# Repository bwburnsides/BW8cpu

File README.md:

# 👾 BW8cpu

The BW8cpu is a homemade CPU built with discrete TTL logic chips on custom designed PCBs. It has a target clock rate of approximately 6 MHz, and is comparable to the Motorola 6809, and more specifically the Hitachi 6309. A larger computer system is built around the CPU in the form a full peripheral suite that allows the BW8cpu to perform as an integrated computer similar to the Commodore 64 and NES. From a hardware perspective, the BW8cpu exceeds these systems in capability and usability in most regards. Its my hope that the system will eventually exceed its predecessors from a software perspective as well.

The project is originally inspired by Ben Eater's [8-bit breadboard CPU](https://eater.net/8bit) and his [breadboard MOS 6502 computer](https://eater.net/6502). However, ultimately the micro-architecture takes more cues from James Sharman's [8-bit pipelined CPU](https://www.youtube.com/watch?v=3iHag4k4yEg&list=PLFhc0MFC8MiCDOh3cGFji3qQfXziB9yOw). This project would not be possible without the support of many individuals present on James Sharman's Discord server, notably [rj45](https://github.com/rj45/rj32), Quandary, Artentus, and [Louis Jewett](https://www.youtube.com/channel/UCsxBT-Jh5pMDU-uEN_EUXtg/featured).

This project is extremely ambitious and long running. This repository will maintain documentation and descriptions of the existent and planned features, as well as supporting schematics and source code files.

--- 

## Features

- 8-bit CPU with 16-bit addressing
- Up to 768 opcodes across 50+ instructions (CISC ISA)
- Dual 8-bit accumulators (A, B) accessible also as one 16-bit accumulator (E)
- Two additional 8-bit General Purpose Registers (C, D)
- Full 16-bit Stack Pointer (SP) and Program Counters (PC)
- Configurable Direct Page addressing (movable Zero Page)
- Two 16-bit Index Registers (X, Y)
- 32-function ALU with 4 flags (Carry, Zero, Overflow, Sign)
- Single IRQ source
- Partially configurable hardware memory map
- Writable Control Store

---
## Architecture Overview

- [von Neumann architecture](https://en.wikipedia.org/wiki/Von_Neumann_architecture) with shared program and data address space
- Vertical microcode (heavily encoded) with 32-bit Control Bus
- Direct to address bus assertions without MAR
- No instruction pipelining - up to 8 clocks / instruction

---

## Expansion & Peripherals

- IO is memory mapped
- Reference Memory Map features:
    - 8 KB shadow RAM kernel space
    - 256 bytes IO space
    - 21.75 KB fixed RAM space
    - 2 KB stack space
    - 32 KB total bankable space
- Plans for full peripheral suite:
    - Programmable Interrupt Controller with 8 interrupt sources
    - VGA Video Card with output at 320x240
    - PS/2 keyboard input
    - Programmable Sound Generator with 4 voices
    - SPI Controller for SD card-based persistent storage
    - RS-232 UART networking interface

---

## Tool Chain

- Simulation with [Digital](https://github.com/hneemann/Digital)
- Emulation with [Rust](https://www.rust-lang.org/)
- Schematics and PCB layout with [KiCAD](https://www.kicad.org/)
- Assembler with [customasm](https://github.com/hlorenzi/customasm)
- Microcode development with customasm
- High level programming with [MHL](https://github.com/Artentus/MHL)

---

## Explore

🔧 [ISA](docs/instruction-set-architecture.md)

🧮 [ALU](docs/arithmetic-logic-unit.md)

🚥 [CU](docs/control-unit.md)

📺 [VGA](docs/video-card.md)

💾 [SPI](docs/spi.md)

📢 [PSG](docs/sound-card.md)

📡 [UART](docs/uart.md)

🎛 [Emulator](docs/emulator.md)

🎯 [Simulator](docs/simulator.md)

🗺 [Memory Map](docs/memory-map.md)

🏗 [Assembler](docs/assembler.md)

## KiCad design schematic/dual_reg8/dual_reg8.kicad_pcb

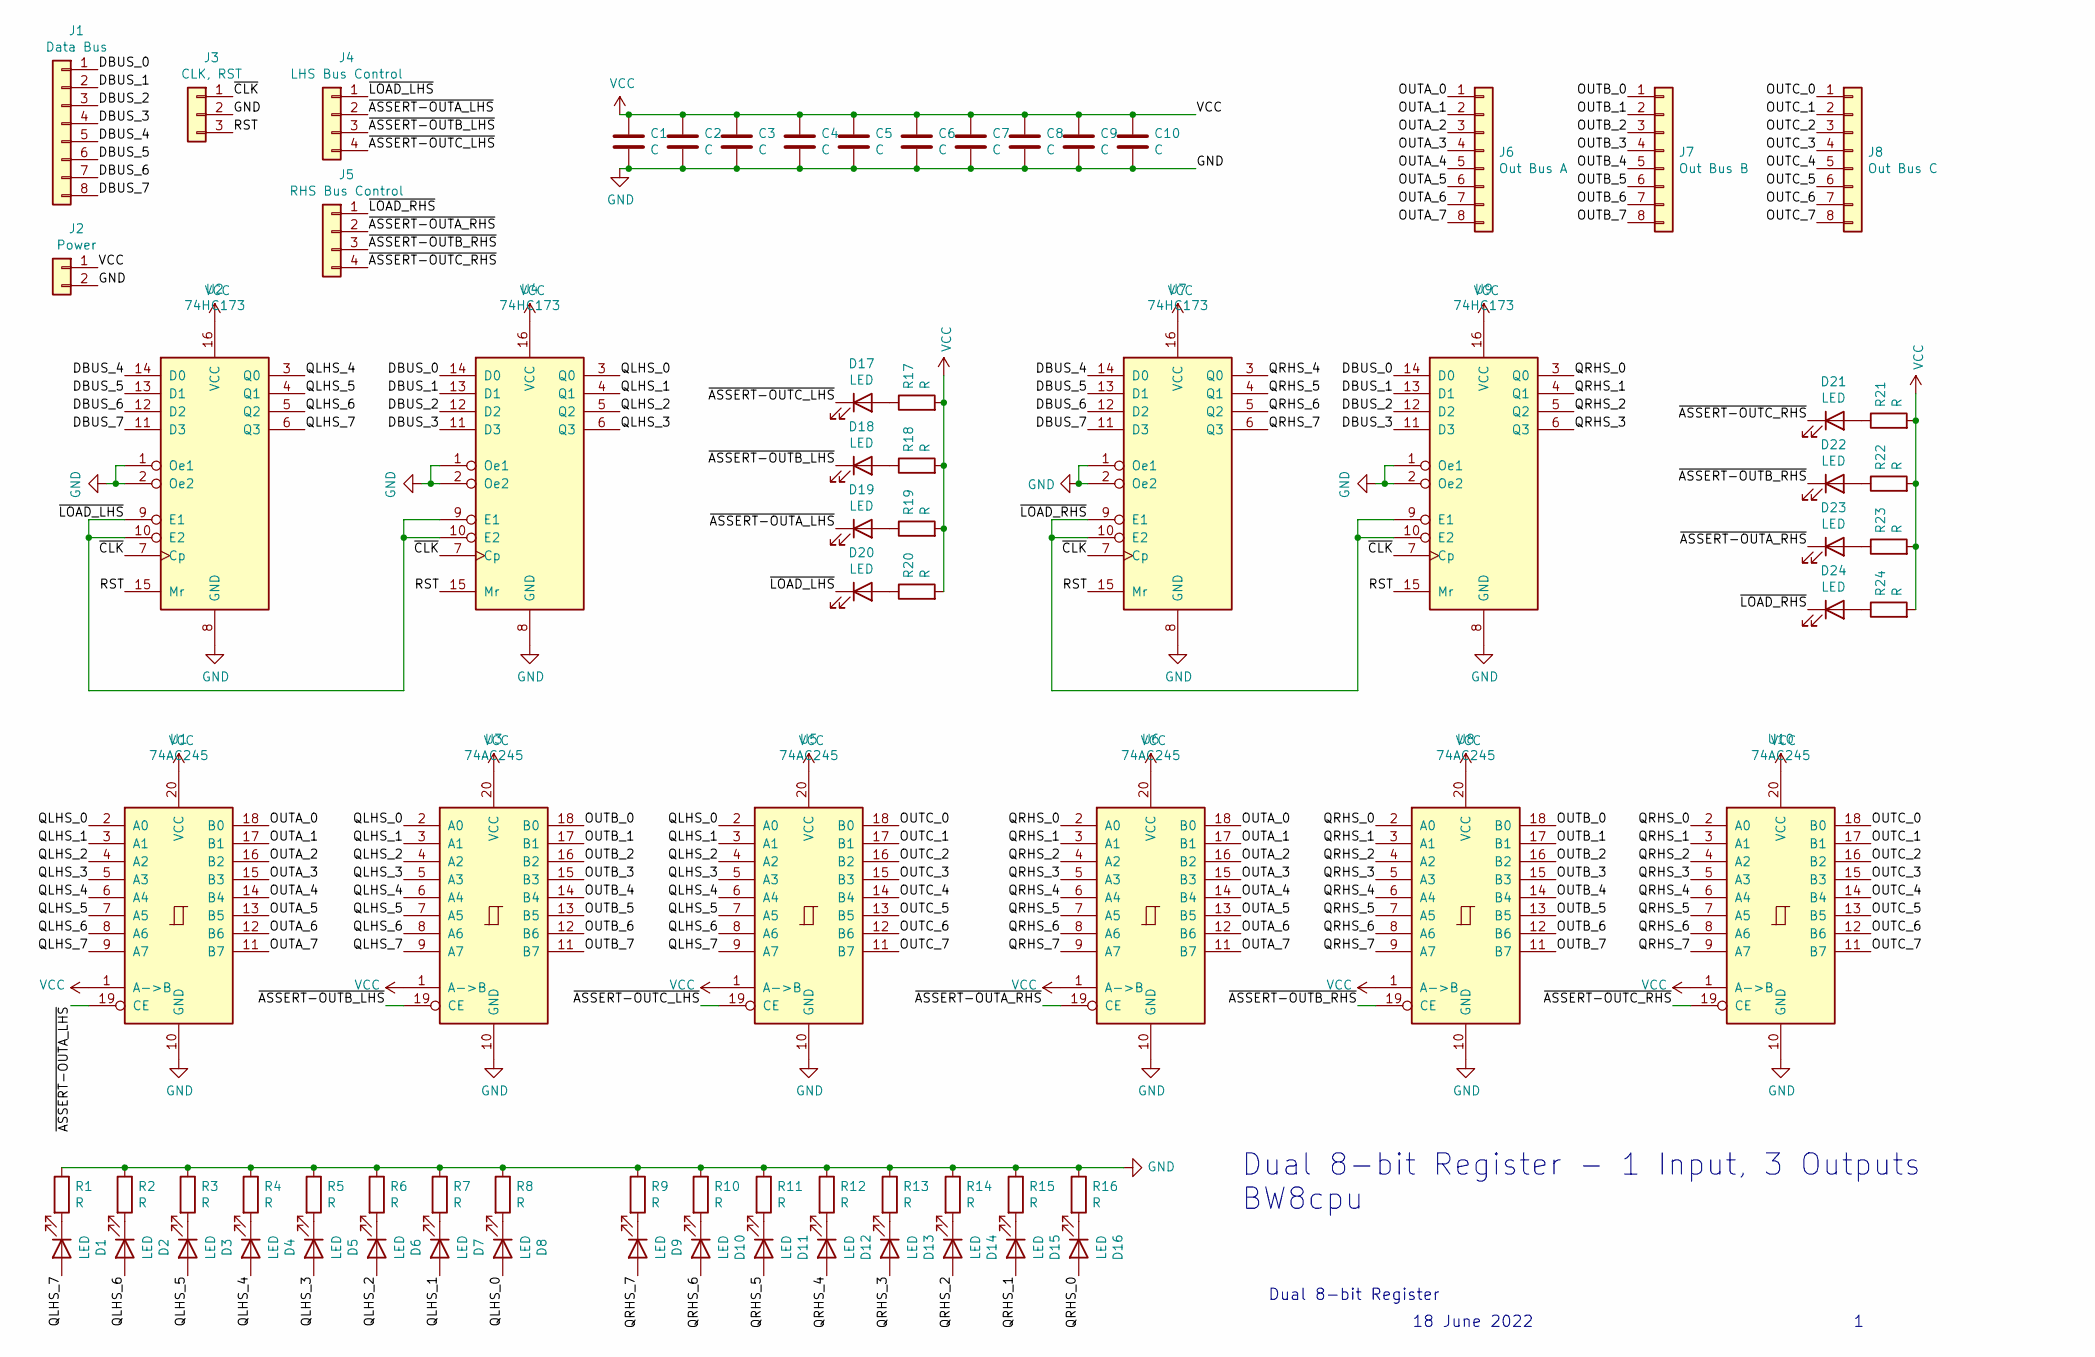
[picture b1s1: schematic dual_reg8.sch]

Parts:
C1, C2, C3, C4, C5, C6, C7, C8, C9, C10: C; C_Disc_D3.0mm_W1.6mm_P2.50mm
D1, D2, D3, D4, D5, D6, D7, D8, D9, D10, D11, D12, D13, D14, D15, D16, D17, D18, D19, D20, D21, D22, D23, D24: LED; LED_D2.0mm_W4.8mm_H2.5mm_FlatTop
J1: Data Bus; PinSocket_1x08_P2.54mm_Vertical
J2: Power; PinSocket_1x02_P2.54mm_Vertical
J3: CLK, RST; PinSocket_1x03_P2.54mm_Vertical
J4: LHS Bus Control; PinSocket_1x04_P2.54mm_Vertical
J5: RHS Bus Control; PinSocket_1x04_P2.54mm_Vertical
J6: Out Bus A; PinSocket_1x08_P2.54mm_Vertical
J7: Out Bus B; PinSocket_1x08_P2.54mm_Vertical
J8: Out Bus C; PinSocket_1x08_P2.54mm_Vertical
R1, R2, R3, R4, R5, R6, R7, R8, R9, R10, R11, R12, R13, R14, R15, R16, R17, R18, R19, R20, R21, R22, R23, R24: R; R_Axial_DIN0204_L3.6mm_D1.6mm_P5.08mm_Horizontal
U1, U3, U5, U6, U8, U10: 74AC245; DIP-20_W7.62mm
U2, U4, U7, U9: 74HC173; DIP-16_W7.62mm

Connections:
/DBUS_0: J1.1, U4.14 (D0), U9.14 (D0)
/DBUS_1: J1.2, U4.13 (D1), U9.13 (D1)
/DBUS_2: J1.3, U4.12 (D2), U9.12 (D2)
/DBUS_3: J1.4, U4.11 (D3), U9.11 (D3)
/DBUS_4: J1.5, U2.14 (D0), U7.14 (D0)
/DBUS_5: J1.6, U2.13 (D1), U7.13 (D1)
/DBUS_6: J1.7, U2.12 (D2), U7.12 (D2)
/DBUS_7: J1.8, U2.11 (D3), U7.11 (D3)
/OUTA_0: J6.1, U1.18 (B0), U6.18 (B0)
/OUTA_1: J6.2, U1.17 (B1), U6.17 (B1)
/OUTA_2: J6.3, U1.16 (B2), U6.16 (B2)
/OUTA_3: J6.4, U1.15 (B3), U6.15 (B3)
/OUTA_4: J6.5, U1.14 (B4), U6.14 (B4)
/OUTA_5: J6.6, U1.13 (B5), U6.13 (B5)
/OUTA_6: J6.7, U1.12 (B6), U6.12 (B6)
/OUTA_7: J6.8, U1.11 (B7), U6.11 (B7)
/OUTB_0: J7.1, U3.18 (B0), U8.18 (B0)
/OUTB_1: J7.2, U3.17 (B1), U8.17 (B1)
/OUTB_2: J7.3, U3.16 (B2), U8.16 (B2)
/OUTB_3: J7.4, U3.15 (B3), U8.15 (B3)
/OUTB_4: J7.5, U3.14 (B4), U8.14 (B4)
/OUTB_5: J7.6, U3.13 (B5), U8.13 (B5)
/OUTB_6: J7.7, U3.12 (B6), U8.12 (B6)
/OUTB_7: J7.8, U3.11 (B7), U8.11 (B7)
/OUTC_0: J8.1, U5.18 (B0), U10.18 (B0)
/OUTC_1: J8.2, U5.17 (B1), U10.17 (B1)
/OUTC_2: J8.3, U5.16 (B2), U10.16 (B2)
/OUTC_3: J8.4, U5.15 (B3), U10.15 (B3)
/OUTC_4: J8.5, U5.14 (B4), U10.14 (B4)
/OUTC_5: J8.6, U5.13 (B5), U10.13 (B5)
/OUTC_6: J8.7, U5.12 (B6), U10.12 (B6)
/OUTC_7: J8.8, U5.11 (B7), U10.11 (B7)
/QLHS_0: D8.2 (A), U1.2 (A0), U3.2 (A0), U4.3 (Q0), U5.2 (A0)
/QLHS_1: D7.2 (A), U1.3 (A1), U3.3 (A1), U4.4 (Q1), U5.3 (A1)
/QLHS_2: D6.2 (A), U1.4 (A2), U3.4 (A2), U4.5 (Q2), U5.4 (A2)
/QLHS_3: D5.2 (A), U1.5 (A3), U3.5 (A3), U4.6 (Q3), U5.5 (A3)
/QLHS_4: D4.2 (A), U1.6 (A4), U2.3 (Q0), U3.6 (A4), U5.6 (A4)
/QLHS_5: D3.2 (A), U1.7 (A5), U2.4 (Q1), U3.7 (A5), U5.7 (A5)
/QLHS_6: D2.2 (A), U1.8 (A6), U2.5 (Q2), U3.8 (A6), U5.8 (A6)
/QLHS_7: D1.2 (A), U1.9 (A7), U2.6 (Q3), U3.9 (A7), U5.9 (A7)
/QRHS_0: D16.2 (A), U6.2 (A0), U8.2 (A0), U9.3 (Q0), U10.2 (A0)
/QRHS_1: D15.2 (A), U6.3 (A1), U8.3 (A1), U9.4 (Q1), U10.3 (A1)
/QRHS_2: D14.2 (A), U6.4 (A2), U8.4 (A2), U9.5 (Q2), U10.4 (A2)
/QRHS_3: D13.2 (A), U6.5 (A3), U8.5 (A3), U9.6 (Q3), U10.5 (A3)
/QRHS_4: D12.2 (A), U6.6 (A4), U7.3 (Q0), U8.6 (A4), U10.6 (A4)
/QRHS_5: D11.2 (A), U6.7 (A5), U7.4 (Q1), U8.7 (A5), U10.7 (A5)
/QRHS_6: D10.2 (A), U6.8 (A6), U7.5 (Q2), U8.8 (A6), U10.8 (A6)
/QRHS_7: D9.2 (A), U6.9 (A7), U7.6 (Q3), U8.9 (A7), U10.9 (A7)
/RST: J3.3, U2.15 (Mr), U4.15 (Mr), U7.15 (Mr), U9.15 (Mr)
/~ASSERT-OUTA_LHS: D19.1 (K), J4.2, U1.19 (CE)
/~ASSERT-OUTA_RHS: D23.1 (K), J5.2, U6.19 (CE)
/~ASSERT-OUTB_LHS: D18.1 (K), J4.3, U3.19 (CE)
/~ASSERT-OUTB_RHS: D22.1 (K), J5.3, U8.19 (CE)
/~ASSERT-OUTC_LHS: D17.1 (K), J4.4, U5.19 (CE)
/~ASSERT-OUTC_RHS: D21.1 (K), J5.4, U10.19 (CE)
/~CLK: J3.1, U2.7 (Cp), U4.7 (Cp), U7.7 (Cp), U9.7 (Cp)
/~LOAD_LHS: D20.1 (K), J4.1, U2.9 (E1), U2.10 (E2), U4.9 (E1), U4.10 (E2)
/~LOAD_RHS: D24.1 (K), J5.1, U7.9 (E1), U7.10 (E2), U9.9 (E1), U9.10 (E2)
GND: C1.2, C2.2, C3.2, C4.2, C5.2, C6.2, C7.2, C8.2, C9.2, C10.2, J2.2, J3.2, R1.1, R2.1, R3.1, R4.1, R5.1, R6.1, R7.1, R8.1, R9.1, R10.1, R11.1, R12.1, R13.1, R14.1, R15.1, R16.1, U1.10 (GND), U2.1 (Oe1), U2.2 (Oe2), U2.8 (GND), U3.10 (GND), U4.1 (Oe1), U4.2 (Oe2), U4.8 (GND), U5.10 (GND), U6.10 (GND), U7.1 (Oe1), U7.2 (Oe2), U7.8 (GND), U8.10 (GND), U9.1 (Oe1), U9.2 (Oe2), U9.8 (GND), U10.10 (GND)
unnamed: D1.1 (K), R1.2
unnamed: D2.1 (K), R2.2
unnamed: D3.1 (K), R3.2
unnamed: D4.1 (K), R4.2
unnamed: D5.1 (K), R5.2
unnamed: D6.1 (K), R6.2
unnamed: D7.1 (K), R7.2
unnamed: D8.1 (K), R8.2
unnamed: D9.1 (K), R9.2
unnamed: D10.1 (K), R10.2
unnamed: D11.1 (K), R11.2
unnamed: D12.1 (K), R12.2
unnamed: D13.1 (K), R13.2
unnamed: D14.1 (K), R14.2
unnamed: D15.1 (K), R15.2
unnamed: D16.1 (K), R16.2
unnamed: D17.2 (A), R17.1
unnamed: D18.2 (A), R18.1
unnamed: D19.2 (A), R19.1
unnamed: D20.2 (A), R20.1
unnamed: D21.2 (A), R21.1
unnamed: D22.2 (A), R22.1
unnamed: D23.2 (A), R23.1
unnamed: D24.2 (A), R24.1
VCC: C1.1, C2.1, C3.1, C4.1, C5.1, C6.1, C7.1, C8.1, C9.1, C10.1, J2.1, R17.2, R18.2, R19.2, R20.2, R21.2, R22.2, R23.2, R24.2, U1.1 (A->B), U1.20 (VCC), U2.16 (VCC), U3.1 (A->B), U3.20 (VCC), U4.16 (VCC), U5.1 (A->B), U5.20 (VCC), U6.1 (A->B), U6.20 (VCC), U7.16 (VCC), U8.1 (A->B), U8.20 (VCC), U9.16 (VCC), U10.1 (A->B), U10.20 (VCC)

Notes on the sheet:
Dual 8-bit Register - 1 Input, 3 Outputs BW8cpu
18 June 2022
Dual 8-bit Register

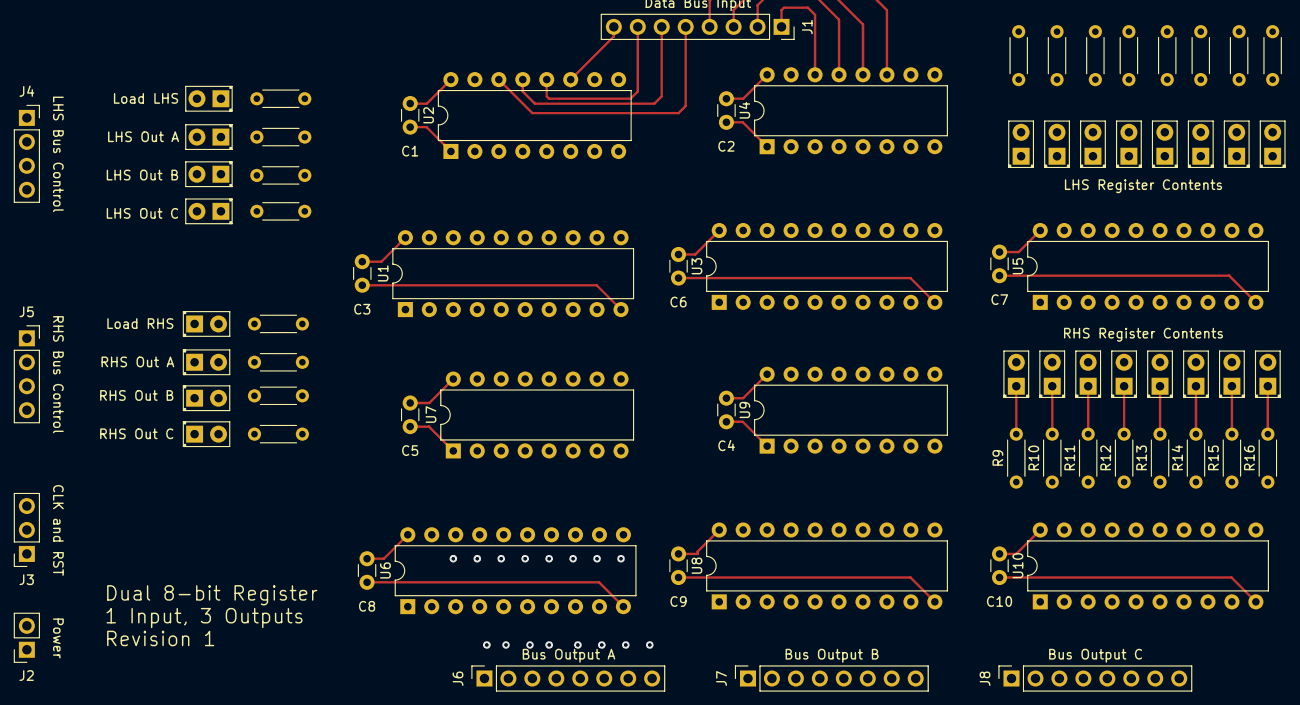
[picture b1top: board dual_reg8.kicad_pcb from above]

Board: 2 copper layers, 76 parts (0 on the bottom side), 84 nets.

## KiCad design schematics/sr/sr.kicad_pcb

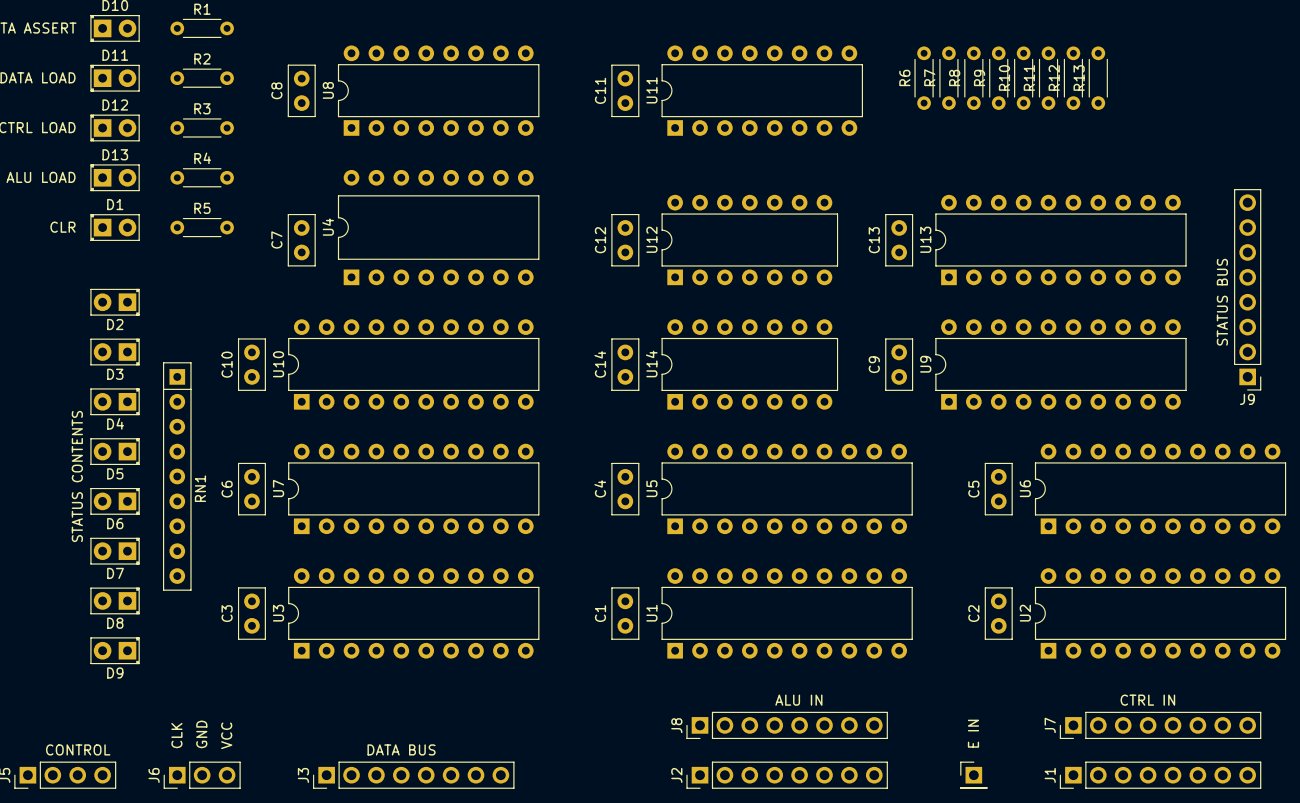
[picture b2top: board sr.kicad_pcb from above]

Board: 2 copper layers, 64 parts (0 on the bottom side), 108 nets, no tracks yet.

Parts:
C1, C2, C3, C4, C5, C6, C7, C8, C9, C10, C11, C12, C13, C14: C_Small; C_Disc_D5.0mm_W2.5mm_P2.50mm
D1, D2, D3, D4, D5, D6, D7, D8, D9, D10, D11, D12, D13: LED; LED_D2.0mm_W4.8mm_H2.5mm_FlatTop
J1, J2, J3, J7, J8, J9: Conn_01x08; PinHeader_1x08_P2.54mm_Vertical
J4: Conn_01x01; PinHeader_1x01_P2.54mm_Vertical
J5: Conn_01x04; PinHeader_1x04_P2.54mm_Vertical
J6: Conn_01x03; PinHeader_1x03_P2.54mm_Vertical
R1, R2, R3, R4, R5, R6, R7, R8, R9, R10, R11, R12, R13: R_Small; R_Axial_DIN0204_L3.6mm_D1.6mm_P5.08mm_Horizontal
RN1: R_Network08; R_Array_SIP9
U1, U2, U3, U5, U6, U7, U9, U10, U13: 74LS245; DIP-20_W7.62mm
U4: 74LS139; DIP-16_W10.16mm
U8, U11: 74LS173; DIP-16_W7.62mm
U12, U14: 74LS126; DIP-14_W7.62mm

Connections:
/ALU_C: J2.7, U1.8
/ALU_E_C: J8.7, U5.8
/ALU_E_I: J8.2, U5.3
/ALU_E_L: J8.3, U5.4
/ALU_E_N: J8.4, U5.5
/ALU_E_V: J8.5, U5.6
/ALU_E_Z: J8.6, U5.7
/ALU_E_x: J8.8, U5.9
/ALU_I: J2.2, U1.3
/ALU_L: J2.3, U1.4
/ALU_N: J2.4, U1.5
/ALU_V: J2.5, U1.6
/ALU_Z: J2.6, U1.7
/ALU_x: J2.8, U1.9
/CLK: J6.1, U8.7, U11.7
/CLR: D1.2, J5.4, U8.15, U11.15
/CTRL_C: J1.7, U2.8
/CTRL_E_C: J7.7, U6.8
/CTRL_E_I: J7.2, U6.3
/CTRL_E_L: J7.3, U6.4
/CTRL_E_N: J7.4, U6.5
/CTRL_E_V: J7.5, U6.6
/CTRL_E_Z: J7.6, U6.7
/CTRL_E_x: J7.8, U6.9
/CTRL_I: J1.2, U2.3
/CTRL_L: J1.3, U2.4
/CTRL_N: J1.4, U2.5
/CTRL_V: J1.5, U2.6
/CTRL_Z: J1.6, U2.7
/CTRL_x: J1.8, U2.9
/DBUS_C: J3.7, U3.8, U10.12
/DBUS_E: J3.1, U3.2, U10.18
/DBUS_I: J3.2, U3.3, U10.17
/DBUS_L: J3.3, U3.4, U10.16
/DBUS_N: J3.4, U3.5, U10.15
/DBUS_V: J3.5, U3.6, U10.14
/DBUS_Z: J3.6, U3.7, U10.13
/DBUS_x: J3.8, U3.9, U10.11
/EBUS0: U5.18, U6.18, U7.18, U12.1
/EBUS1: U5.17, U6.17, U7.17, U12.4
/EBUS2: U5.16, U6.16, U7.16, U12.10
/EBUS3: U5.15, U6.15, U7.15, U12.13
/EBUS4: U5.14, U6.14, U7.14, U14.1
/EBUS5: U5.13, U6.13, U7.13, U14.4
/EBUS6: U5.12, U6.12, U7.12, U14.10
/EBUS7: U5.11, U6.11, U7.11, U14.13
/F0: R6.1, U11.14, U12.3
/F1: R7.1, U11.13, U12.6
/F2: R8.1, U11.12, U12.8
/F3: R9.1, U11.11, U12.11
/F4: R10.1, U8.14, U14.3
/F5: R11.1, U8.13, U14.6
/F6: R12.1, U8.12, U14.8
/F7: R13.1, U8.11, U14.11
/FBUS0: U1.18, U2.18, U3.18, U12.2
/FBUS1: U1.17, U2.17, U3.17, U12.5
/FBUS2: U1.16, U2.16, U3.16, U12.9
/FBUS3: U1.15, U2.15, U3.15, U12.12
/FBUS4: U1.14, U2.14, U3.14, U14.2
/FBUS5: U1.13, U2.13, U3.13, U14.5
/FBUS6: U1.12, U2.12, U3.12, U14.9
/FBUS7: U1.11, U2.11, U3.11, U14.12
/GND: C1.2, C2.2, C3.2, C4.2, C5.2, C6.2, C7.2, C8.2, C9.2, C10.2, C11.2, C12.2, C13.2, C14.2, J6.2, R5.1, RN1.1, U1.10, U2.10, U3.10, U4.1, U4.8, U5.10, U6.10, U7.10, U8.1, U8.2, U8.8, U8.9, U8.10, U9.10, U9.19, U10.10, U11.1, U11.2, U11.8, U11.9, U11.10, U12.7, U13.10, U13.19, U14.7
/IDX_E: J4.1, U1.2, U2.2
/LED0: D2.2, U13.18
/LED1: D3.2, U13.17
/LED2: D4.2, U13.16
/LED3: D5.2, U13.15
/LED4: D6.2, U13.14
/LED5: D7.2, U13.13
/LED6: D8.2, U13.12
/LED7: D9.2, U13.11
/Q0: R6.2, U9.2, U10.2, U11.3, U13.2
/Q1: R7.2, U9.3, U10.3, U11.4, U13.3
/Q2: R8.2, U9.4, U10.4, U11.5, U13.4
/Q3: R9.2, U9.5, U10.5, U11.6, U13.5
/Q4: R10.2, U8.3, U9.6, U10.6, U13.6
/Q5: R11.2, U8.4, U9.7, U10.7, U13.7
/Q6: R12.2, U8.5, U9.8, U10.8, U13.8
/Q7: R13.2, U8.6, U9.9, U10.9, U13.9
/S0: J9.1, U9.18
/S1: J9.2, U9.17
/S2: J9.3, U9.16
/S3: J9.4, U9.15
/S4: J9.5, U9.14
/S5: J9.6, U9.13
/S6: J9.7, U9.12
/S7: J9.8, U9.11
/SRC_SELECT0: J5.1, U4.2
/SRC_SELECT1: J5.2, U4.3
/VCC: C1.1, C2.1, C3.1, C4.1, C5.1, C6.1, C7.1, C8.1, C9.1, C10.1, C11.1, C12.1, C13.1, C14.1, J6.3, R1.2, R2.2, R3.2, R4.2, U1.1, U1.20, U2.1, U2.20, U3.1, U3.20, U4.16, U5.1, U5.2, U5.20, U6.1, U6.2, U6.20, U7.1, U7.2, U7.3, U7.4, U7.5, U7.6, U7.7, U7.8, U7.9, U7.20, U8.16, U9.1, U9.20, U10.1, U10.20, U11.16, U12.14, U13.1, U13.20, U14.14
/~ALU_SELECT: D13.1, U1.19, U4.4, U5.19
/~CTRL_SELECT: D12.1, U2.19, U4.5, U6.19
/~DBUS_ASSERT: D10.1, J5.3, U10.19
/~DBUS_SELECT: D11.1, U3.19, U4.6, U7.19
unnamed: D1.1, R5.2
unnamed: D2.1, RN1.2
unnamed: D3.1, RN1.3
unnamed: D4.1, RN1.4
unnamed: D5.1, RN1.5
unnamed: D6.1, RN1.6
unnamed: D7.1, RN1.7
unnamed: D8.1, RN1.8
unnamed: D9.1, RN1.9
unnamed: D10.2, R1.1
unnamed: D11.2, R2.1
unnamed: D12.2, R3.1
unnamed: D13.2, R4.1

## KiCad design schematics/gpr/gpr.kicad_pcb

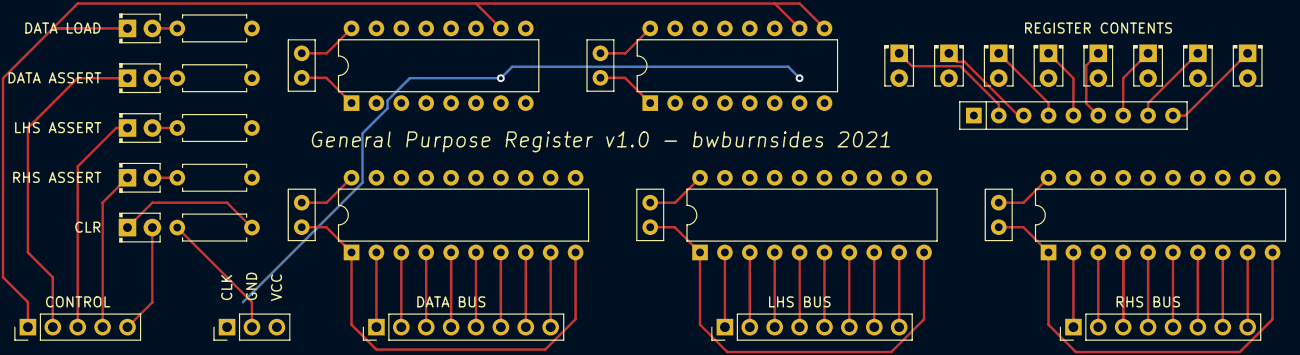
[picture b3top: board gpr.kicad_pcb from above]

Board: 2 copper layers, 34 parts (0 on the bottom side), 53 nets.

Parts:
C1, C2, C3, C4, C5: C_Small; C_Disc_D5.0mm_W2.5mm_P2.50mm
CtrlHdr1: Conn_01x05; PinHeader_1x05_P2.54mm_Vertical
D1, D2, D3, D4, D5, D6, D7, D8, D9, D10, D11, D12, D13: LED; LED_D2.0mm_W4.0mm_H2.8mm_FlatTop
DHdr1: Conn_01x08; PinHeader_1x08_P2.54mm_Vertical
DataDriver1: 74LS245; DIP-20_W7.62mm
LHSDriver1: 74LS245; DIP-20_W7.62mm
LHSHdr1: Conn_01x08; PinHeader_1x08_P2.54mm_Vertical
PwrHdr1: Conn_01x03; PinHeader_1x03_P2.54mm_Vertical
R1, R2, R3, R4, R5: R; R_Axial_DIN0207_L6.3mm_D2.5mm_P7.62mm_Horizontal
RHSDriver1: 74LS245; DIP-20_W7.62mm
RHSHdr1: Conn_01x08; PinHeader_1x08_P2.54mm_Vertical
RegHi1: 74LS173; DIP-16_W7.62mm
RegLEDRes1: R_Network08; R_Array_SIP9
RegLo1: 74LS173; DIP-16_W7.62mm

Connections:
/B0: D6.2, DataDriver1.18, LHSDriver1.18, RHSDriver1.18, RegLo1.3
/B1: D7.2, DataDriver1.17, LHSDriver1.17, RHSDriver1.17, RegLo1.4
/B2: D8.2, DataDriver1.16, LHSDriver1.16, RHSDriver1.16, RegLo1.5
/B3: D9.2, DataDriver1.15, LHSDriver1.15, RHSDriver1.15, RegLo1.6
/B4: D10.2, DataDriver1.14, LHSDriver1.14, RHSDriver1.14, RegHi1.3
/B5: D11.2, DataDriver1.13, LHSDriver1.13, RHSDriver1.13, RegHi1.4
/B6: D12.2, DataDriver1.12, LHSDriver1.12, RHSDriver1.12, RegHi1.5
/B7: D13.2, DataDriver1.11, LHSDriver1.11, RHSDriver1.11, RegHi1.6
/CLK: PwrHdr1.1, RegHi1.7, RegLo1.7
/CLR: CtrlHdr1.5, D1.2, RegHi1.15, RegLo1.15
/D0: DHdr1.1, DataDriver1.2, RegLo1.14
/D1: DHdr1.2, DataDriver1.3, RegLo1.13
/D2: DHdr1.3, DataDriver1.4, RegLo1.12
/D3: DHdr1.4, DataDriver1.5, RegLo1.11
/D4: DHdr1.5, DataDriver1.6, RegHi1.14
/D5: DHdr1.6, DataDriver1.7, RegHi1.13
/D6: DHdr1.7, DataDriver1.8, RegHi1.12
/D7: DHdr1.8, DataDriver1.9, RegHi1.11
/GND: C1.2, C2.2, C3.2, C4.2, C5.2, DataDriver1.1, DataDriver1.10, LHSDriver1.1, LHSDriver1.10, PwrHdr1.2, R5.1, RHSDriver1.1, RHSDriver1.10, RegHi1.1, RegHi1.2, RegHi1.8, RegLEDRes1.1, RegLo1.1, RegLo1.2, RegLo1.8
/L0: LHSDriver1.2, LHSHdr1.1
/L1: LHSDriver1.3, LHSHdr1.2
/L2: LHSDriver1.4, LHSHdr1.3
/L3: LHSDriver1.5, LHSHdr1.4
/L4: LHSDriver1.6, LHSHdr1.5
/L5: LHSDriver1.7, LHSHdr1.6
/L6: LHSDriver1.8, LHSHdr1.7
/L7: LHSDriver1.9, LHSHdr1.8
/R0: RHSDriver1.2, RHSHdr1.1
/R1: RHSDriver1.3, RHSHdr1.2
/R2: RHSDriver1.4, RHSHdr1.3
/R3: RHSDriver1.5, RHSHdr1.4
/R4: RHSDriver1.6, RHSHdr1.5
/R5: RHSDriver1.7, RHSHdr1.6
/R6: RHSDriver1.8, RHSHdr1.7
/R7: RHSDriver1.9, RHSHdr1.8
/VCC: C1.1, C2.1, C3.1, C4.1, C5.1, DataDriver1.20, LHSDriver1.20, PwrHdr1.3, R1.2, R2.2, R3.2, R4.2, RHSDriver1.20, RegHi1.16, RegLo1.16
/~DBUS_ASSERT: CtrlHdr1.2, D3.1, DataDriver1.19
/~DBUS_LOAD: CtrlHdr1.1, D2.1, RegHi1.9, RegHi1.10, RegLo1.9, RegLo1.10
/~LHS_ASSERT: CtrlHdr1.3, D4.1, LHSDriver1.19
/~RHS_ASSERT: CtrlHdr1.4, D5.1, RHSDriver1.19
unnamed: D1.1, R5.2
unnamed: D2.2, R1.1
unnamed: D3.2, R2.1
unnamed: D4.2, R3.1
unnamed: D5.2, R4.1
unnamed: D6.1, RegLEDRes1.2
unnamed: D7.1, RegLEDRes1.3
unnamed: D8.1, RegLEDRes1.4
unnamed: D9.1, RegLEDRes1.5
unnamed: D10.1, RegLEDRes1.6
unnamed: D11.1, RegLEDRes1.7
unnamed: D12.1, RegLEDRes1.8
unnamed: D13.1, RegLEDRes1.9

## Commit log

2021-03-16 initial checkin for project
2021-03-30 moved existing logisim circuit to sap1.circ, began custom design in existing file
2021-03-30 checkin of output 7segment display rom writer
2021-03-30 development of initial plans in dev log (not finished or up to date)
2021-03-30 removal of original logisim file (contents live in sap file now)
2021-03-30 gitignore checkin, now blocking .bin files
2021-04-07 initial control logic development
2021-05-07 cleaned of dev log files and updated readme. new memory map planning doc.
2021-05-07 new vga planning post
2021-05-07 additional vga/font dev support files
2021-05-07 support file checkin, new living doc in font_codes.md for modified PETSCII map
2021-05-07 initial checkin of experimental Logisim "vga card"
2021-07-13 cleaned up graphics folder
2021-07-13 asm folder cleanup
2021-07-13 sound folder cleanup
2021-07-13 isa folder cleanup
2021-07-13 mem folder cleanup
2021-07-13 docs cleanup
2021-07-13 gitignore update, dont track pdf or txt
2021-07-13 architecture update post
2021-11-18 checkin kicad schematics
2021-11-18 updated gitignore
2021-11-18 digital simulation checkin
2021-11-18 asm changes checkin
2021-11-18 docs changes checkin
2021-11-18 removed some schematic and all logisim files
2021-11-18 removed isa folder and contents
2021-11-18 readme update
2021-11-18 renamed asm folder to assembler
2021-11-18 removed scripts folder
2021-11-18 remove memory-map folder
2021-11-18 removed devlog
2021-11-18 cleanup ucode folder
2021-11-18 initial cleanup of control lines
2021-11-23 repo cleanup
2021-11-23 rename emulator package name
2021-11-23 rename readme to lowercase bc anal
2021-11-23 simulator progression
2021-11-23 grammar changes
2021-11-24 additional simulation components (alu logic and shift)
2021-11-24 more information regarding memory map
2021-11-26 more progress on simulator, additional registers and bus controller rework
2021-11-26 updated arch diagram
2021-11-26 better wording in readme
2021-11-27 new ctrl encodings for DPI and SPI constants
2022-01-01 slight cleanup. divided opcodes into instruction pages.
2022-01-05 microcode progress
2022-01-13 progress on microcode compiler
2022-01-13 microcode changes
2022-01-14 assembler definition beginnings!
2022-01-14 more assembly definitions
2022-01-18 additional microcode
2022-01-18 new microcode subruledefs to expand macro capabilities
2022-01-19 split microcode into separate #ruledefs
2022-01-20 new bitfield patterns for subruledef in microcode assembly file
2022-01-23 reordered state input to put flags lower order than opcode for easier microcode generation. new customasm updated with once and fn
2022-01-23 updated opcode assigner to include secondary byte to denote which instruction page each instruction belongs to
2022-01-24 replaced JSR Ind with JSR X and Y
2022-02-07 updated assembly definition
2022-02-07 cpu mode controller checkin
2022-02-22 simulation updates (ALU in testing now)
2022-03-07 simulation intermittedely "compiles" in Digital. Problem with RHS bus.
2022-03-09 simulation progress - rudimentary microcode is executing!
2022-03-12 updated memory map description to current plans
2022-03-12 corrected image issue in mem map doc
2022-03-13 cpu simulation now starting in semi consistent zero state
2022-03-13 cleaned up simulation layout and updated readme
2022-03-15 new reduced instruction set that fits in 2^9 bits
2022-03-15 fixed readme pointing to wrong image
2022-03-15 new reduced instruction set documentation
2022-03-15 fixed first order formatting errors in reduced isa documentation doc
2022-03-15 added first order sub section links to reduced ISA doc
2022-03-15 added STORE instruction information to ISA docs
2022-03-15 byte definition of a full instruction in ISA doc
2022-03-16 added cmp imm opcodes, removed shr wo carry
2022-03-28 updated assembler to match new instruction set
2022-03-28 remove old asm file
2022-04-05 updated ISA, control lines, and simulation files
2022-04-21 continued work on simulator
2022-04-21 remove old microcode/ and instruction/ folders in favor of new control/
2022-04-21 may as well commit these emulator files
2022-04-21 start of an assembly standard library
2022-04-21 new ISA docs. needs further revisions.
2022-04-21 fixed spacing in assembler definition file
2022-04-21 added #once decl to def and opcodes file
2022-04-30 more type annotations in microcode
2022-05-17 ugh so much
2022-05-18 fixed out instruction syntax and byte ordering. changed IO port syntax.
2022-05-22 working simulator!
2022-05-29 simulator changes - now working spurious load glitch
2022-06-03 python emulator progress
2022-06-04 mass commit to clean source tree
2022-06-04 emulator progress
2022-06-04 new C emulator
2022-06-05 C emulator progress
2022-06-05 added flag loading from bus
2022-06-05 remove python emulator
2022-06-06 refactor control line debugging
2022-06-08 emulator work
2022-06-08 initial commit of new emulator
2022-06-08 git problems
2022-06-10 tentatively... should support most of instruction set
2022-06-11 emulator and simulator work
2022-06-11 emulator test suite and black autoformatting
2022-06-13 microcode updates and corresponding changes in emulator
2022-06-15 nested namespaces
2022-06-15 converted structs and namespaces to classes
2022-06-17 new simulator baseline
2022-06-18 tentative new commit to fix offsets
2022-06-18 sim not crashing with 173s in address adder
2022-06-18 xfer-dbus driving and bank register
2022-06-20 mega simulator progress
2022-06-22 digital automated testing
2022-06-24 emulator changes
2022-06-24 emulator work, UART partially working
2022-06-29 working UART!
2022-06-29 SR fixed for interrupts
2022-07-02 microcode updates
2022-07-02 switching branches, cleaning tree
2022-07-03 initial reduced microcode implementation. mem bus contention issue.
2022-08-27 cleaning source tree to switch branches
2022-09-08 removed DP opcodes, added SWI and IO opcodes
